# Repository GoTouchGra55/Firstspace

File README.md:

# Firstspace (Electronics)

Firstspace is an electric GoKart developed by the BigBrain group.

## Overview

The electric GoKart consists of all custom electronics which includes an electronic speec controller (ESC), battery management system (BMS), and a control system based on an STM32-based micro-controller chip.

See [Schematics](Electronics/ESC/ESC.pdf)

## Routing

This is a 6 layer pcb.

## Features

### ESC Core

- STM32F405 Cortex-M4 MCU
- Upto 168 MHz CPU clock
- Hall effect auxiliary connectors
- Upto 3 ESC outputs
- Auxiliary communications and servo connectors

## Authors 👥

Shaurya (Electronics)  
Contact: [Email](shauryatamang.dev@gmail.com)

Krish (CAD)
View: [Github](https://github.com/unknowngamer69/)

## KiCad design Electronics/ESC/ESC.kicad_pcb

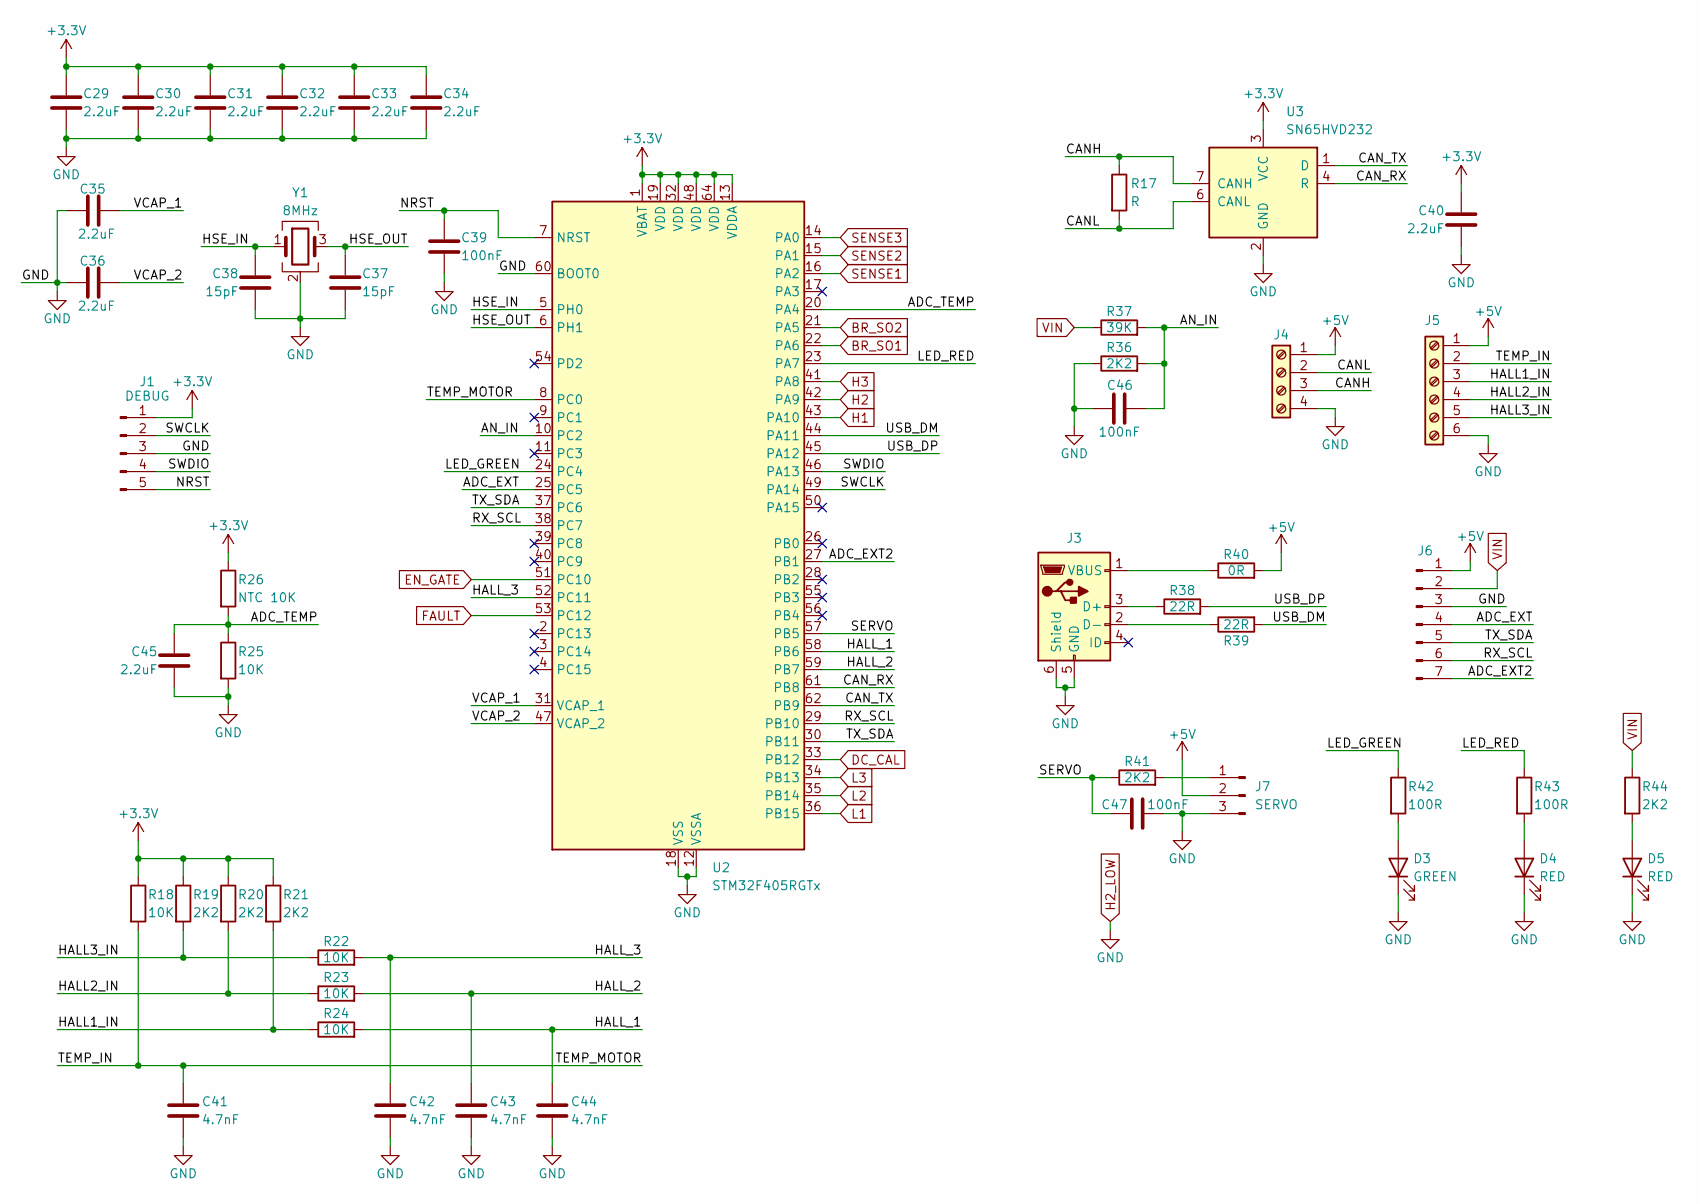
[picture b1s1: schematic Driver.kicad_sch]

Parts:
C29, C30, C31, C32, C33, C34, C35, C36, C40, C45: 2.2uF; C_0603_1608Metric
C37, C38: 15pF; C_0603_1608Metric
C39, C46, C47: 100nF; C_0603_1608Metric
C41, C42, C43, C44: 4.7nF; C_0603_1608Metric
D3: GREEN; LED_0603_1608Metric
D4, D5: RED; LED_0603_1608Metric
J1: DEBUG; JST_XH_B5B-XH-AM_1x05_P2.50mm_Vertical
J3: USB_B_Micro; USB_Micro-B_Molex_47346-0001
J4: Screw_Terminal_01x04; JST_XH_S4B-XH-A_1x04_P2.50mm_Horizontal
J5: Screw_Terminal_01x06; JST_XH_S6B-XH-A_1x06_P2.50mm_Horizontal
J6: Conn_01x07_Pin; JST_XH_S7B-XH-A-1_1x07_P2.50mm_Horizontal
J7: SERVO; JST_XH_S3B-XH-A_1x03_P2.50mm_Horizontal
R17: R; R_0603_1608Metric
R18, R22, R23, R24, R25: 10K; R_0603_1608Metric
R19, R20, R21, R36, R41, R44: 2K2; R_0603_1608Metric
R26: NTC 10K; R_0603_1608Metric
R37: 39K; R_0603_1608Metric
R38, R39: 22R; R_0603_1608Metric
R40: 0R; R_0603_1608Metric
R42, R43: 100R; R_0603_1608Metric
U2: STM32F405RGTx; LQFP-64_10x10mm_P0.5mm
U3: SN65HVD232; SOIC-8_3.9x4.9mm_P1.27mm
Y1: 8MHz; Crystal_SMD_3225-4Pin_3.2x2.5mm

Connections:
+3.3V: C29.1, C30.1, C31.1, C32.1, C33.1, C34.1, C40.1, J1.1, R18.1, R19.1, R20.1, R21.1, R26.1, U2.1 (VBAT), U2.13 (VDDA), U2.19 (VDD), U2.32 (VDD), U2.48 (VDD), U2.64 (VDD), U3.3 (VCC); also elsewhere on the board
+5V: J4.1, J5.1, J6.1, J7.2, R40.2; also elsewhere on the board
/Driver/ADC_EXT: J6.4, U2.25 (PC5)
/Driver/ADC_EXT2: J6.7, U2.27 (PB1)
/Driver/ADC_TEMP: C45.1, R25.1, R26.2, U2.20 (PA4)
/Driver/AN_IN: C46.2, R36.2, R37.2, U2.10 (PC2)
/Driver/CANH: J4.3, R17.1, U3.7 (CANH)
/Driver/CANL: J4.2, R17.2, U3.6 (CANL)
/Driver/CAN_RX: U2.61 (PB8), U3.4 (R)
/Driver/CAN_TX: U2.62 (PB9), U3.1 (D)
/Driver/HALL1_IN: J5.3, R21.2, R24.1
/Driver/HALL2_IN: J5.4, R20.2, R23.1
/Driver/HALL3_IN: J5.5, R19.2, R22.1
/Driver/HALL_1: C44.1, R24.2, U2.58 (PB6)
/Driver/HALL_2: C43.1, R23.2, U2.59 (PB7)
/Driver/HALL_3: C42.1, R22.2, U2.52 (PC11)
/Driver/HSE_IN: C38.1, U2.5 (PH0), Y1.1
/Driver/HSE_OUT: C37.1, U2.6 (PH1), Y1.3
/Driver/LED_GREEN: R42.1, U2.24 (PC4)
/Driver/LED_RED: R43.1, U2.23 (PA7)
/Driver/NRST: C39.1, J1.5, U2.7 (NRST)
/Driver/RX_SCL: J6.6, U2.29 (PB10), U2.38 (PC7)
/Driver/SERVO: C47.1, R41.1, U2.57 (PB5)
/Driver/SWCLK: J1.2, U2.49 (PA14)
/Driver/SWDIO: J1.4, U2.46 (PA13)
/Driver/TEMP_IN: C41.1, J5.2, R18.2, U2.8 (PC0)
/Driver/TX_SDA: J6.5, U2.30 (PB11), U2.37 (PC6)
/Driver/USB_DM: R39.2, U2.44 (PA11)
/Driver/USB_DP: R38.2, U2.45 (PA12)
/Driver/VCAP_1: C35.1, U2.31 (VCAP_1)
/Driver/VCAP_2: C36.1, U2.47 (VCAP_2)
BR_SO1: U2.22 (PA6); also elsewhere on the board
BR_SO2: U2.21 (PA5); also elsewhere on the board
DC_CAL: U2.33 (PB12); also elsewhere on the board
EN_GATE: U2.51 (PC10); also elsewhere on the board
FAULT: U2.53 (PC12); also elsewhere on the board
H1: U2.43 (PA10); also elsewhere on the board
H2: U2.42 (PA9); also elsewhere on the board
H2_LOW: C29.2, C30.2, C31.2, C32.2, C33.2, C34.2, C35.2, C36.2, C37.2, C38.2, C39.2, C40.2, C41.2, C42.2, C43.2, C44.2, C45.2, C46.1, C47.2, D3.1 (K), D4.1 (K), D5.1 (K), J1.3, J3.5 (GND), J3.6 (Shield), J4.4, J5.6, J6.3, J7.3, R25.2, R36.1, U2.12 (VSSA), U2.18 (VSS), U2.60 (BOOT0), U2.63 (VSS), U3.2 (GND), Y1.2 (G), Y1.4 (G); also elsewhere on the board
H3: U2.41 (PA8); also elsewhere on the board
L1: U2.36 (PB15); also elsewhere on the board
L2: U2.35 (PB14); also elsewhere on the board
L3: U2.34 (PB13); also elsewhere on the board
unnamed: D3.2 (A), R42.2
unnamed: D4.2 (A), R43.2
unnamed: D5.2 (A), R44.2
unnamed: J3.3 (D+), R38.1
unnamed: J3.2 (D-), R39.1
unnamed: J3.1 (VBUS), R40.1
unnamed: J7.1, R41.2
SENSE1: U2.16 (PA2); also elsewhere on the board
SENSE2: U2.15 (PA1); also elsewhere on the board
SENSE3: U2.14 (PA0); also elsewhere on the board
VIN: J6.2, R37.1, R44.1; also elsewhere on the board

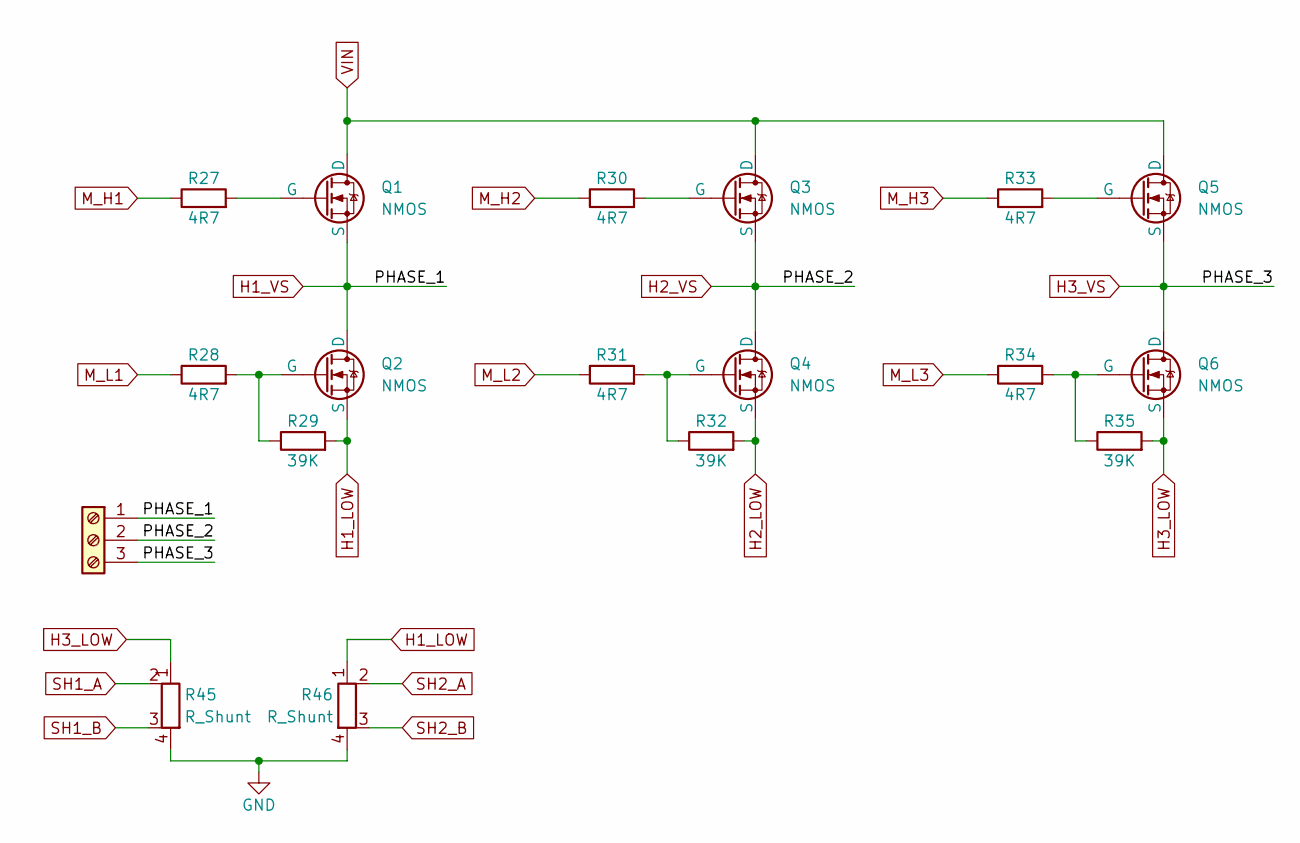
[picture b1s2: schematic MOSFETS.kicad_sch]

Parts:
J2: Screw_Terminal_01x03; TerminalBlock_Phoenix_MKDS-1,5-3-5.08_1x03_P5.08mm_Horizont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
Q1, Q2, Q3, Q4, Q5, Q6: NMOS; TRANS_IRF3205S
R27, R28, R30, R31, R33, R34: 4R7; R_0603_1608Metric
R29, R32, R35: 39K; R_0603_1608Metric
R45, R46: R_Shunt; R_Shunt_Ohmite_LVK20

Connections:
H1_LOW: Q2.3 (S), R29.2, R46.1; also elsewhere on the board
H1_VS: J2.1, Q1.3 (S), Q2.1 (D); also elsewhere on the board
H2_LOW: Q4.3 (S), R32.2, R45.4, R46.4; also elsewhere on the board
H2_VS: J2.2, Q3.3 (S), Q4.1 (D); also elsewhere on the board
H3_LOW: Q6.3 (S), R35.2, R45.1; also elsewhere on the board
H3_VS: J2.3, Q5.3 (S), Q6.1 (D); also elsewhere on the board
M_H1: R27.1; also elsewhere on the board
M_H2: R30.1; also elsewhere on the board
M_H3: R33.1; also elsewhere on the board
M_L1: R28.1; also elsewhere on the board
M_L2: R31.1; also elsewhere on the board
M_L3: R34.1; also elsewhere on the board
unnamed: Q1.2 (G), R27.2
unnamed: Q2.2 (G), R28.2, R29.1
unnamed: Q3.2 (G), R30.2
unnamed: Q4.2 (G), R31.2, R32.1
unnamed: Q5.2 (G), R33.2
unnamed: Q6.2 (G), R34.2, R35.1
SH1_A: R45.2; also elsewhere on the board
SH1_B: R45.3; also elsewhere on the board
SH2_A: R46.2; also elsewhere on the board
SH2_B: R46.3; also elsewhere on the board
VIN: Q1.1 (D), Q3.1 (D), Q5.1 (D); also elsewhere on the board

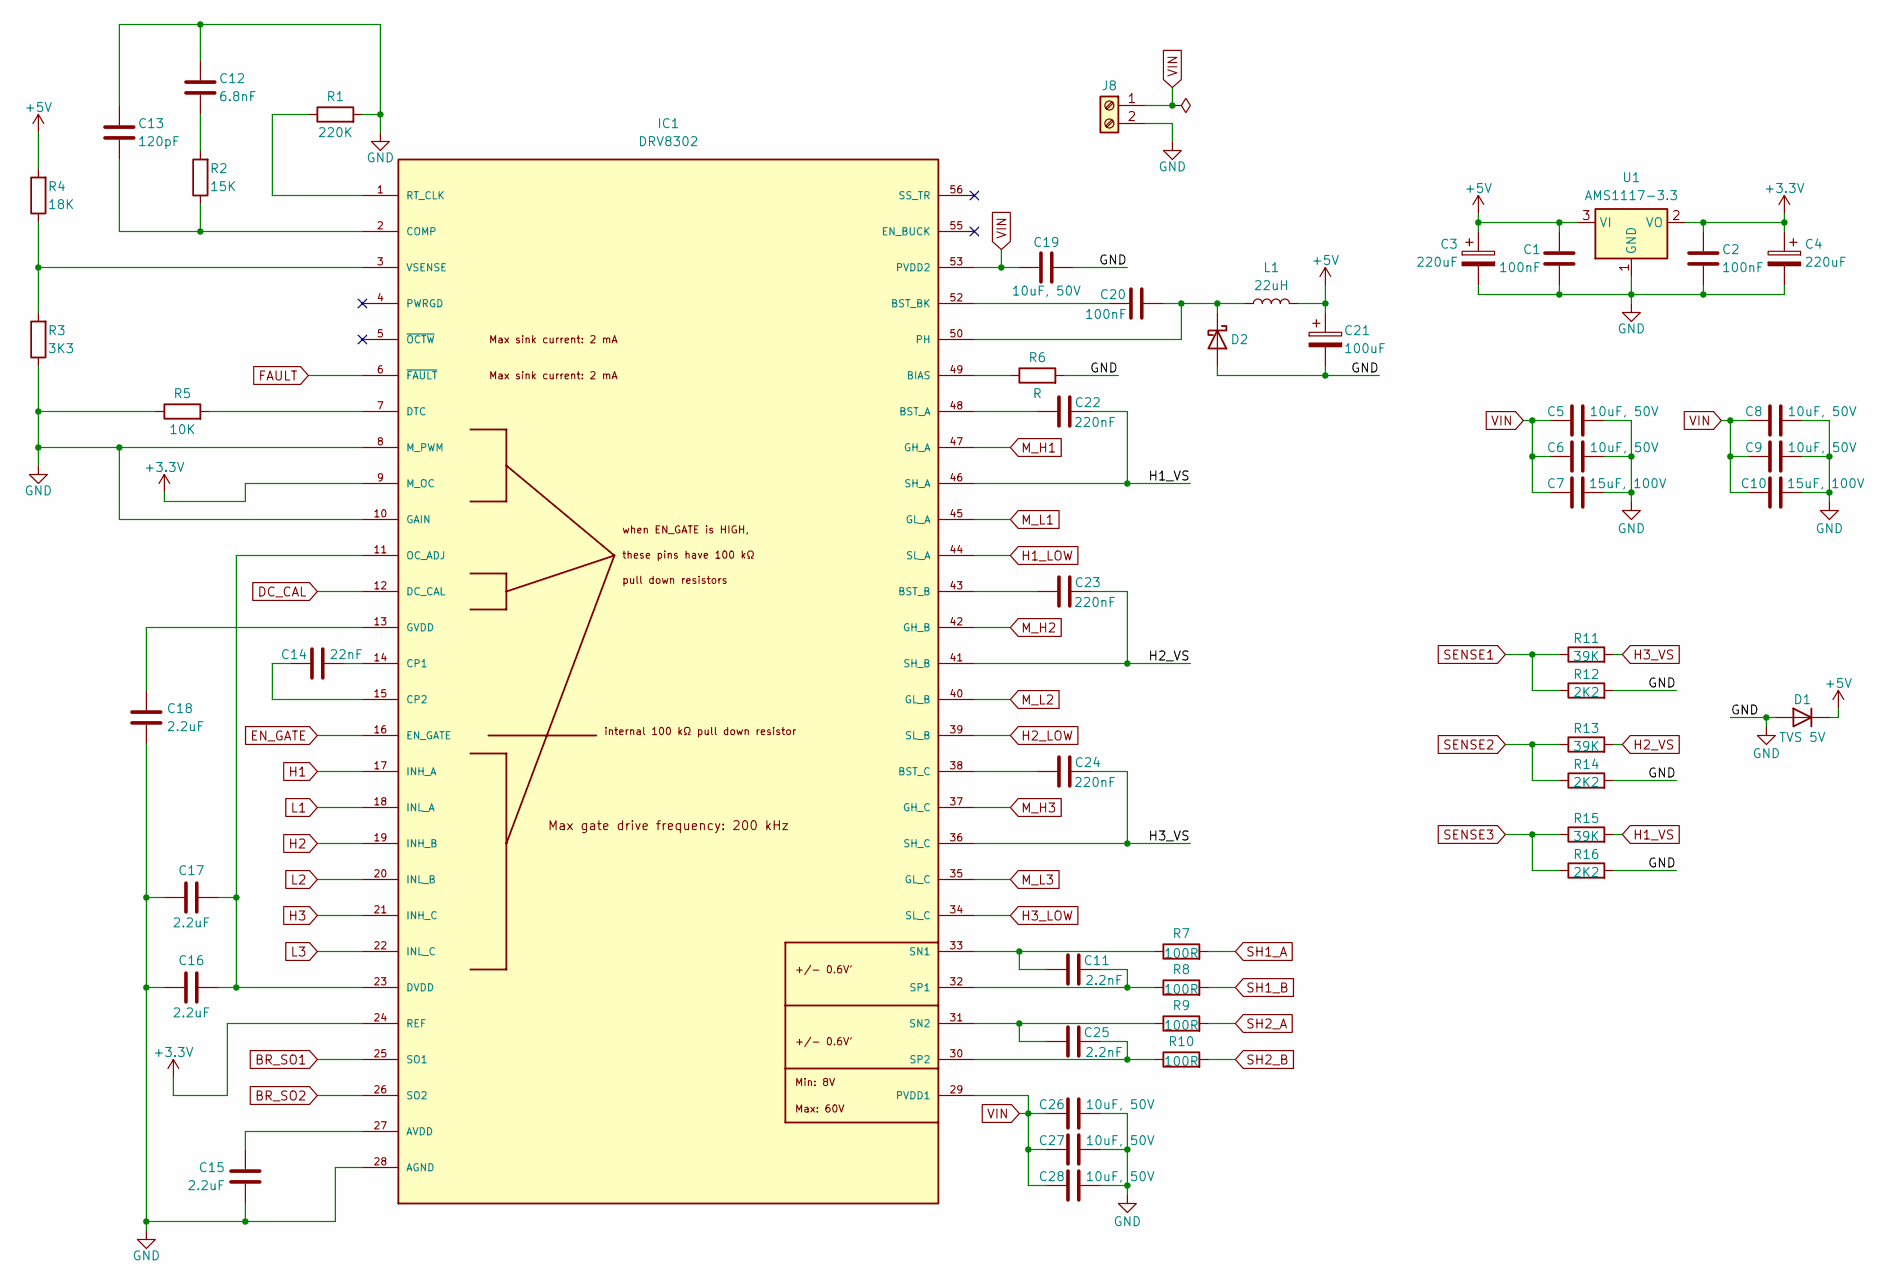
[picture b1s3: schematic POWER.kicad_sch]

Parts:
C1, C2, C20: 100nF; C_0603_1608Metric
C3, C4: 220uF; C_0805_2012Metric
C5, C6, C8, C9, C19, C26, C27, C28: 10uF, 50V; C_0603_1608Metric
C7, C10: 15uF, 100V; C_0603_1608Metric
C11, C25: 2.2nF; C_0603_1608Metric
C12: 6.8nF; C_0603_1608Metric
C13: 120pF; C_0603_1608Metric
C14: 22nF; C_0603_1608Metric
C15, C16, C17, C18: 2.2uF; C_0603_1608Metric
C21: 100uF; C_0805_2012Metric
C22, C23, C24: 220nF; C_0603_1608Metric
D1: TVS 5V; D_0603_1608Metric
D2: D_Schottky; D_0603_1608Metric
IC1: DRV8302; HTSSOP-56-1EP_6.1x14mm_P0.5mm_EP3.61x6.35mm
J8: Screw_Terminal_01x02; TerminalBlock_Phoenix_MKDS-1,5-2-5.08_1x02_P5.08mm_Horizont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
L1: 22uH; L_Cenker_CKCS5040
R1: 220K; R_0805_2012Metric
R2: 15K; R_0603_1608Metric
R3: 3K3; R_0603_1608Metric
R4: 18K; R_0603_1608Metric
R5: 10K; R_0603_1608Metric
R6: R; R_0603_1608Metric
R7, R8, R9, R10: 100R; R_0603_1608Metric
R11, R13, R15: 39K; R_0603_1608Metric
R12, R14, R16: 2K2; R_0603_1608Metric
U1: AMS1117-3.3; SOT-223-3_TabPin2

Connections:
+3.3V: C2.1, C4.1, IC1.9 (M_OC), IC1.24 (REF), U1.2 (VO); also elsewhere on the board
+5V: C1.1, C3.1, C21.1, D1.1 (K), L1.2, R4.2, U1.3 (VI); also elsewhere on the board
BR_SO1: IC1.25 (SO1); also elsewhere on the board
BR_SO2: IC1.26 (SO2); also elsewhere on the board
DC_CAL: IC1.12 (DC_CAL); also elsewhere on the board
EN_GATE: IC1.16 (EN_GATE); also elsewhere on the board
FAULT: IC1.6 (~FAULT); also elsewhere on the board
H1: IC1.17 (INH_A); also elsewhere on the board
H1_LOW: IC1.44 (SL_A); also elsewhere on the board
H1_VS: C22.1, IC1.46 (SH_A), R15.2; also elsewhere on the board
H2: IC1.19 (INH_B); also elsewhere on the board
H2_LOW: C1.2, C2.2, C3.2, C4.2, C5.2, C6.2, C7.2, C8.2, C9.2, C10.2, C12.1, C13.1, C15.1, C16.1, C17.1, C18.1, C19.2, C21.2, C26.2, C27.2, C28.2, D1.2 (A), D2.2 (A), IC1.8 (M_PWM), IC1.10 (GAIN), IC1.28 (AGND), IC1.39 (SL_B), IC1.57 (AGND), IC1.58 (AGND), IC1.59 (AGND), J8.2, R1.2, R3.1, R5.1, R6.2, R12.2, R14.2, R16.2, U1.1 (GND); also elsewhere on the board
H2_VS: C23.1, IC1.41 (SH_B), R13.2; also elsewhere on the board
H3: IC1.21 (INH_C); also elsewhere on the board
H3_LOW: IC1.34 (SL_C); also elsewhere on the board
H3_VS: C24.1, IC1.36 (SH_C), R11.2; also elsewhere on the board
L1: IC1.18 (INL_A); also elsewhere on the board
L2: IC1.20 (INL_B); also elsewhere on the board
L3: IC1.22 (INL_C); also elsewhere on the board
M_H1: IC1.47 (GH_A); also elsewhere on the board
M_H2: IC1.42 (GH_B); also elsewhere on the board
M_H3: IC1.37 (GH_C); also elsewhere on the board
M_L1: IC1.45 (GL_A); also elsewhere on the board
M_L2: IC1.40 (GL_B); also elsewhere on the board
M_L3: IC1.35 (GL_C); also elsewhere on the board
unnamed: C12.2, R2.2
unnamed: C20.2, D2.1 (K), IC1.50 (PH), IC1.51 (PH), L1.1
unnamed: C15.2, IC1.27 (AVDD)
unnamed: IC1.49 (BIAS), R6.1
unnamed: C22.2, IC1.48 (BST_A)
unnamed: C23.2, IC1.43 (BST_B)
unnamed: C20.1, IC1.52 (BST_BK)
unnamed: C24.2, IC1.38 (BST_C)
unnamed: C13.2, IC1.2 (COMP), R2.1
unnamed: C14.2, IC1.14 (CP1)
unnamed: C14.1, IC1.15 (CP2)
unnamed: IC1.7 (DTC), R5.2
unnamed: C16.2, C17.2, IC1.11 (OC_ADJ), IC1.23 (DVDD)
unnamed: C18.2, IC1.13 (GVDD)
unnamed: IC1.1 (RT_CLK), R1.1
unnamed: C11.2, IC1.33 (SN1), R7.1
unnamed: C25.2, IC1.31 (SN2), R9.1
unnamed: C11.1, IC1.32 (SP1), R8.1
unnamed: C25.1, IC1.30 (SP2), R10.1
unnamed: IC1.3 (VSENSE), R3.2, R4.1
SENSE1: R11.1, R12.1; also elsewhere on the board
SENSE2: R13.1, R14.1; also elsewhere on the board
SENSE3: R15.1, R16.1; also elsewhere on the board
SH1_A: R7.2; also elsewhere on the board
SH1_B: R8.2; also elsewhere on the board
SH2_A: R9.2; also elsewhere on the board
SH2_B: R10.2; also elsewhere on the board
VIN: C5.1, C6.1, C7.1, C8.1, C9.1, C10.1, C19.1, C26.1, C27.1, C28.1, IC1.29 (PVDD1), IC1.53 (PVDD2), IC1.54 (PVDD2), J8.1; also elsewhere on the board

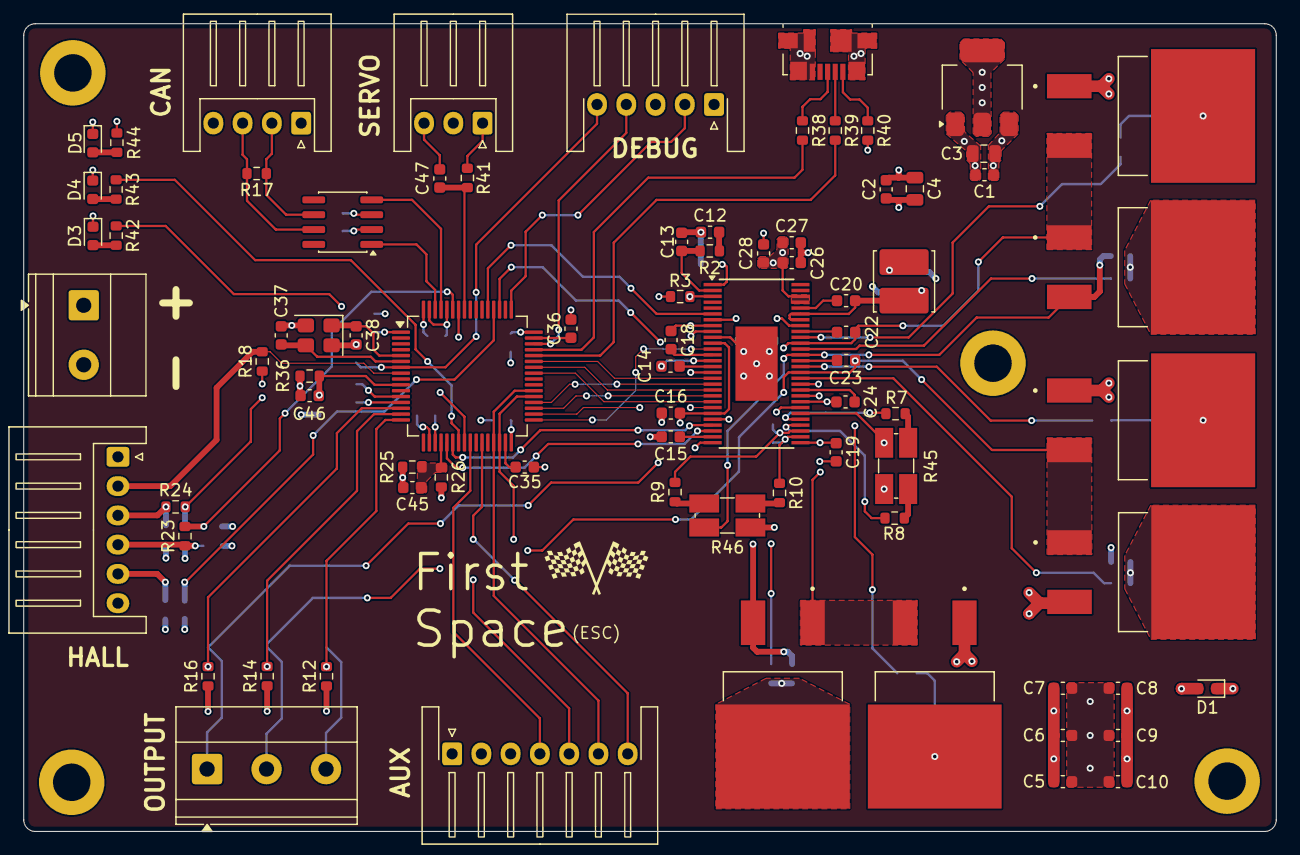
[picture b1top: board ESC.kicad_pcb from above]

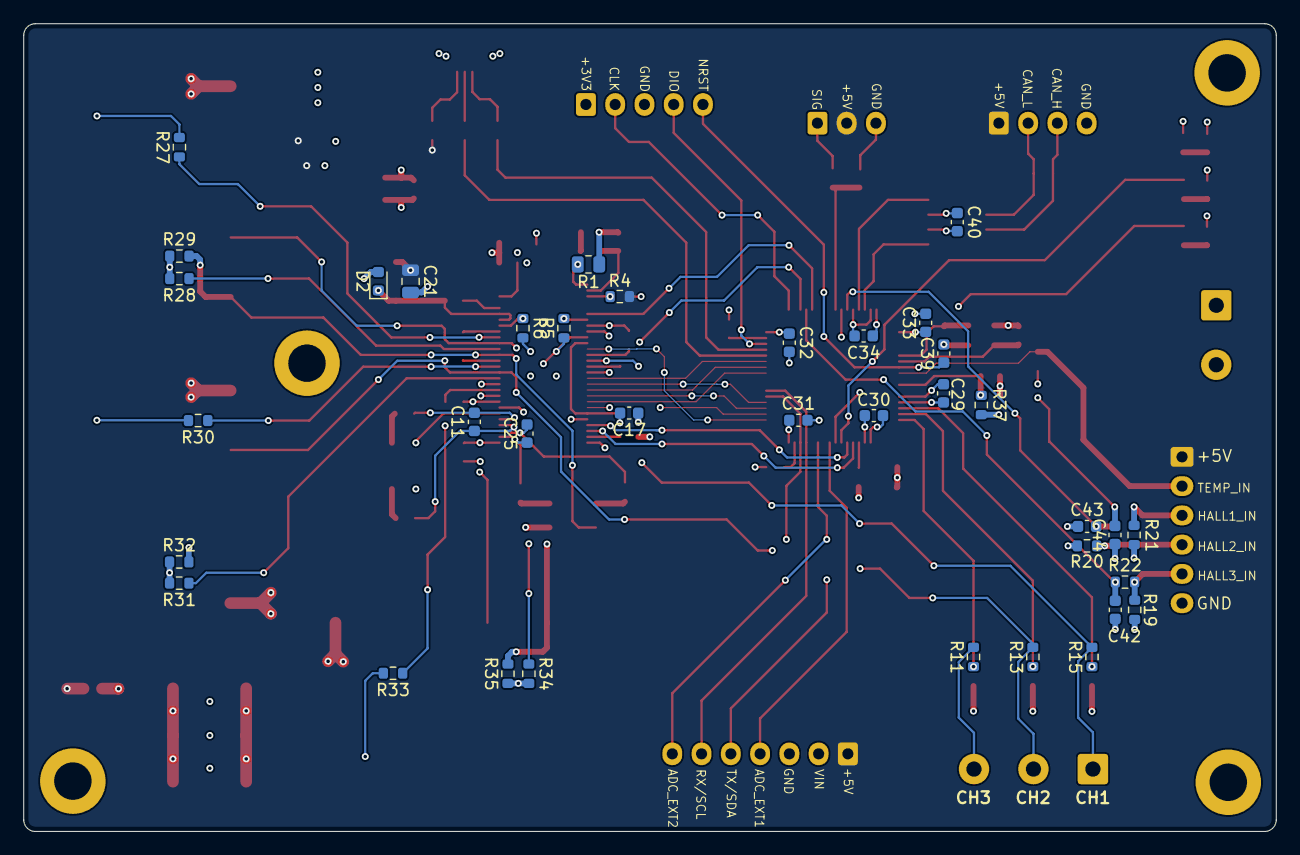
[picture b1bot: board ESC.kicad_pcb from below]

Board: 6 copper layers, 107.0 x 69.0 mm, 117 parts (37 on the bottom side), 95 nets.

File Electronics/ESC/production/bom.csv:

Designator,Footprint,Quantity,Value,LCSC Part #
"C1, C2, C20, C39, C46, C47",0603,6,100nF,
"C10, C7",0603,2,"15uF, 100V",
"C11, C25",0603,2,2.2nF,
C12,0603,1,6.8nF,
C13,0603,1,120pF,
C14,0603,1,22nF,
"C15, C16, C17, C18, C29, C30, C31, C32, C33, C34, C35, C36, C40, C45",0603,14,2.2uF,
"C19, C26, C27, C28, C5, C6, C8, C9",0603,8,"10uF, 50V",
C21,0805,1,100uF,
"C22, C23, C24",0603,3,220nF,
"C3, C4",0805,2,220uF,
"C37, C38",0603,2,15pF,
"C42, C43, C44",0603,3,4.7nF,
D1,0603,1,TVS 5V,
D2,0603,1,D_Schottky,
D3,0603,1,GREEN,
"D4, D5",0603,2,RED,
IC1,HTSSOP-56-1EP_6.1x14mm_P0.5mm_EP3.61x6.35mm,1,DRV8302,
J1,JST_XH_S5B-XH-A-1_1x05_P2.50mm_Horizontal,1,DEBUG,
J2,"TerminalBlock_Phoenix_MKDS-1,5-3-5.08_1x03_P5.08mm_Horizontal",1,Screw_Terminal_01x03,
J3,USB_Micro-B_Molex_47346-0001,1,USB_B_Micro,
J4,JST_XH_S4B-XH-A_1x04_P2.50mm_Horizontal,1,Screw_Terminal_01x04,
J5,JST_XH_S6B-XH-A_1x06_P2.50mm_Horizontal,1,Screw_Terminal_01x06,
J6,JST_XH_S7B-XH-A-1_1x07_P2.50mm_Horizontal,1,Conn_01x07_Pin,
J7,JST_XH_S3B-XH-A_1x03_P2.50mm_Horizontal,1,SERVO,
J8,"TerminalBlock_Phoenix_MKDS-1,5-2-5.08_1x02_P5.08mm_Horizontal",1,Screw_Terminal_01x02,
L1,L_Cenker_CKCS5040,1,22uH,
"Q1, Q2, Q3, Q4, Q5, Q6",TRANS_IRF3205S,6,NMOS,
R1,0805,1,220K,
"R10, R42, R43, R7, R8, R9",0603,6,100R,
"R11, R13, R15, R29, R32, R35, R37",0603,7,39K,
"R12, R14, R16, R19, R20, R21, R36, R41, R44",0603,9,2K2,
"R17, R6",0603,2,R,
"R18, R22, R23, R24, R25, R5",0603,6,10K,
R2,0603,1,15K,
R26,0603,1,NTC 10K,
"R27, R28, R30, R31, R33, R34",0603,6,4R7,
R3,0603,1,3K3,
"R38, R39",0603,2,22R,
R4,0603,1,18K,
R40,0603,1,0R,
"R45, R46",R_Shunt_Ohmite_LVK20,2,R_Shunt,
U1,SOT-223-3_TabPin2,1,AMS1117-3.3,
U2,LQFP-64_10x10mm_P0.5mm,1,STM32F405RGTx,
U3,SOIC-8_3.9x4.9mm_P1.27mm,1,SN65HVD232,
Y1,Crystal_SMD_3225-4Pin_3.2x2.5mm,1,8MHz,
